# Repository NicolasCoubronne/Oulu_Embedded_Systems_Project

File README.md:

# Oulu_Embedded_Systems_Project

## Embedded System Project 2023, group 2

Clone :

git clone https://github.com/NicolasCoubronne/Oulu_Embedded_Systems_Project.git

Pull :

git pull

Push : 

git add *

git commit -m "name of commit"

<<<<<<< HEAD
git push origin main
=======
git push origin main
>>>>>>> 29aacac8a4f2100fd199b27751b34c95d99f8d8b

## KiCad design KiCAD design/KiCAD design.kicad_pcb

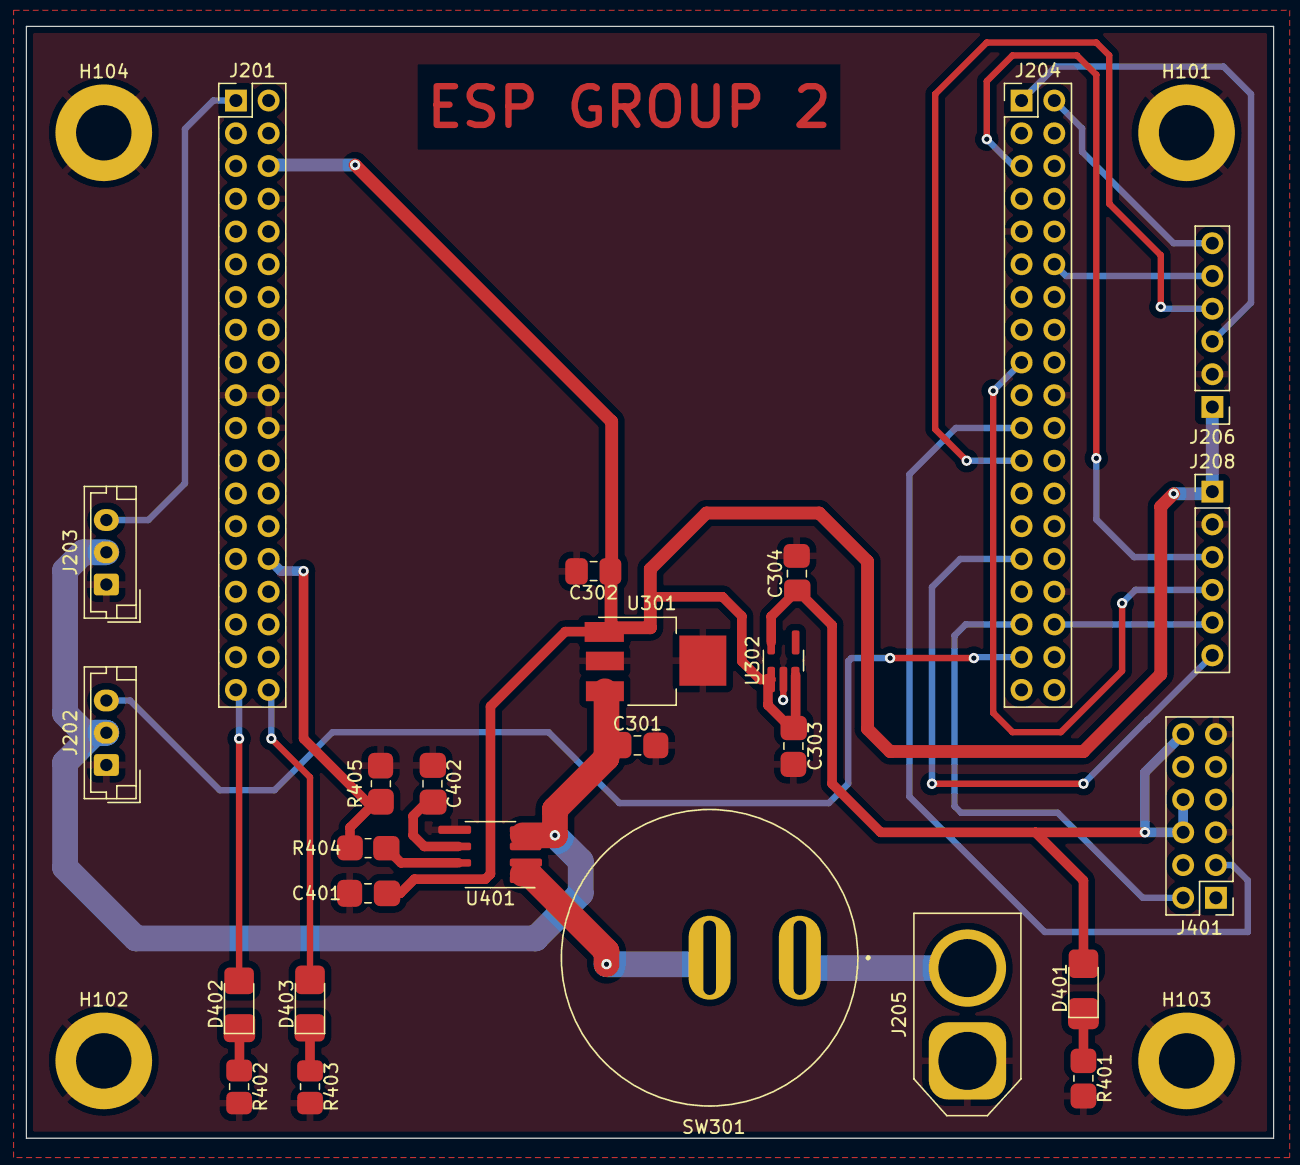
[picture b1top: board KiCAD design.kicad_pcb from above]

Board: 2 copper layers, 96.8 x 86.2 mm, 30 parts (0 on the bottom side), 26 nets.

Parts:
C301, C302, C303, C304: 1uF; C_0805_2012Metric
C401: 0.1uF; C_0805_2012Metric
C402: 1nF; C_0805_2012Metric
D401: GREEN; LED_1206_3216Metric
D402, D403: RED; LED_1206_3216Metric
H101, H102, H103, H104: MountingHole_Pad; MountingHole_4.3mm_M4_DIN965_Pad
J201, J204: Conn_02x19_Odd_Even; PinHeader_2x19_P2.54mm_Vertical
J202, J203: Conn_01x03_Female; JST_EH_B3B-EH-A_1x03_P2.50mm_Vertical
J205: JST BATTERY; AMASS_XT60-M_1x02_P7.20mm_Vertical
J206: JST SENS TOF 2; PinHeader_1x06_P2.54mm_Vertical
J208: JST SENS TOF 1; PinHeader_1x06_P2.54mm_Vertical
J401: Conn_02x06_Top_Bottom; PinHeader_2x06_P2.54mm_Vertical
R401, R402, R403: 330; R_0805_2012Metric
R404: 10k; R_0805_2012Metric
R405: 19.1k; R_0805_2012Metric
SW301: E-SWITCH_RR511D1121
U301: MCP1804T; SOT-223-3_TabPin2
U302: MIC5317; SOT-23-5
U401: ACS712xLCTR-20A; SOIC-8_3.9x4.9mm_P1.27mm

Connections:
+3.3V: C304.1, D401.2 (A), J401.6, J401.8, J401.12, U302.5 (VOUT)
+5V: C302.1, C303.1, C401.2, J201.6, J206.1, J208.1, U301.1 (OUT), U302.1 (VIN), U302.3 (~SHDN), U401.8 (VCC)
+12V: C301.1, J202.2, J203.2, U301.3 (IN), U401.3 (IP-), U401.4 (IP-)
/CONNECTORS/BATT: J205.2, SW301.1 (A)
/CONNECTORS/Bluetooth_RX: J204.33, J401.2
/CONNECTORS/Bluetooth_TX: J204.21, J401.3
/CONNECTORS/CURRENT_MEASURE: J201.30, R404.2, R405.1
/CONNECTORS/LED1: D403.2 (A), J201.38
/CONNECTORS/LED2: D402.2 (A), J201.37
/CONNECTORS/TOF1_DATA_READY: J204.29, J208.6
/CONNECTORS/TOF1_SCL: J204.17, J208.4
/CONNECTORS/TOF1_SDA: J204.5, J208.3
/CONNECTORS/TOF1_XSHUT: J204.34, J208.5
/CONNECTORS/TOF2_DATA_READY: J204.2, J206.6
/CONNECTORS/TOF2_SCL: J204.23, J206.4
/CONNECTORS/TOF2_SDA: J204.1, J206.3
/CONNECTORS/TOF2_XSHUT: J204.12, J206.5
/CONNECTORS/USART_HD_ARM: J202.3, J204.35
/CONNECTORS/USART_HD_BASE: J201.1, J203.3
/ON_BOARD_COMPONENTS/IP+: SW301.2 (B), U401.1 (IP+), U401.2 (IP+)
GND: C301.2, C302.2, C303.2, C304.2, C401.1, C402.1, H101.1, H102.1, H103.1, H104.1, J201.8, J201.19, J201.20, J201.22, J202.1, J203.1, J204.9, J204.20, J204.32, J205.1, J206.2, J208.2, J401.5, J401.11, R401.2, R402.2, R403.2, R405.2, U301.2 (GND), U302.2 (GND), U401.5 (GND)
unnamed: C402.2, U401.6 (FILTER)
unnamed: D401.1 (K), R401.1
unnamed: D402.1 (K), R402.1
unnamed: D403.1 (K), R403.1
unnamed: R404.1, U401.7 (VIOUT)

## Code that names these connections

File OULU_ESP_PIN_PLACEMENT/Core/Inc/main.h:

/* USER CODE BEGIN Header */
/**
  ******************************************************************************
  * @file           : main.h
  * @brief          : Header for main.c file.
  *                   This file contains the common defines of the application.
  ******************************************************************************
  * @attention
  *
  * Copyright (c) 2023 STMicroelectronics.
  * All rights reserved.
  *
  * This software is licensed under terms that can be found in the LICENSE file
  * in the root directory of this software component.
  * If no LICENSE file comes with this software, it is provided AS-IS.
  *
  ******************************************************************************
  */
/* USER CODE END Header */

/* Define to prevent recursive inclusion -------------------------------------*/
#ifndef __MAIN_H
#define __MAIN_H

#ifdef __cplusplus
extern "C" {
#endif

/* Includes ------------------------------------------------------------------*/
#include "stm32f4xx_hal.h"

/* Private includes ----------------------------------------------------------*/
/* USER CODE BEGIN Includes */

/* USER CODE END Includes */

/* Exported types ------------------------------------------------------------*/
/* USER CODE BEGIN ET */

/* USER CODE END ET */

/* Exported constants --------------------------------------------------------*/
/* USER CODE BEGIN EC */

/* USER CODE END EC */

/* Exported macro ------------------------------------------------------------*/
/* USER CODE BEGIN EM */

/* USER CODE END EM */

void HAL_TIM_MspPostInit(TIM_HandleTypeDef *htim);

/* Exported functions prototypes ---------------------------------------------*/
void Error_Handler(void);

/* USER CODE BEGIN EFP */

/* USER CODE END EFP */

/* Private defines -----------------------------------------------------------*/
#define B1_Pin GPIO_PIN_13
#define B1_GPIO_Port GPIOC
#define LED1_Pin GPIO_PIN_0
#define LED1_GPIO_Port GPIOC
#define LED2_Pin GPIO_PIN_3
#define LED2_GPIO_Port GPIOC
#define CURRENT_MEASURE_Pin GPIO_PIN_1
#define CURRENT_MEASURE_GPIO_Port GPIOA
#define USART_TX_ARM_Pin GPIO_PIN_2
#define USART_TX_ARM_GPIO_Port GPIOA
#define LD2_Pin GPIO_PIN_5
#define LD2_GPIO_Port GPIOA
#define TOF1_XHSUT_Pin GPIO_PIN_4
#define TOF1_XHSUT_GPIO_Port GPIOC
#define TOF2_DATA_READY_Pin GPIO_PIN_8
#define TOF2_DATA_READY_GPIO_Port GPIOC
#define TOF2_I2C_SDA_Pin GPIO_PIN_9
#define TOF2_I2C_SDA_GPIO_Port GPIOC
#define TOF2_I2C_SCL_Pin GPIO_PIN_8
#define TOF2_I2C_SCL_GPIO_Port GPIOA
#define BT_TX_Pin GPIO_PIN_9
#define BT_TX_GPIO_Port GPIOA
#define BT_RX_Pin GPIO_PIN_10
#define BT_RX_GPIO_Port GPIOA
#define TOF2_XSHUT_Pin GPIO_PIN_12
#define TOF2_XSHUT_GPIO_Port GPIOA
#define TMS_Pin GPIO_PIN_13
#define TMS_GPIO_Port GPIOA
#define TCK_Pin GPIO_PIN_14
#define TCK_GPIO_Port GPIOA
#define USART_TX_BASE_Pin GPIO_PIN_10
#define USART_TX_BASE_GPIO_Port GPIOC
#define SWO_Pin GPIO_PIN_3
#define SWO_GPIO_Port GPIOB
#define TOF1_DATA_READY_Pin GPIO_PIN_5
#define TOF1_DATA_READY_GPIO_Port GPIOB
#define TOF1_I2C_SCL_Pin GPIO_PIN_6
#define TOF1_I2C_SCL_GPIO_Port GPIOB
#define TOF1_I2C_SDA_Pin GPIO_PIN_9
#define TOF1_I2C_SDA_GPIO_Port GPIOB

/* USER CODE BEGIN Private defines */

/* USER CODE END Private defines */

#ifdef __cplusplus
}
#endif

#endif /* __MAIN_H */

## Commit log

2023-01-20 test
2023-03-07 readme
2023-03-07 Sheets and connectors
2023-03-14 finished conectors / sensors / converters
2023-03-14 labeling and add of components. STM32 pin selected
2023-03-15 servo extender piece (freecad + stl files)
2023-03-15 dont track backups and autosaves (they are different per system, will add changes even if you dont change anything and not needed in version control)
2023-03-15 forget ignored files
2023-03-17 correction pin bluetooth
2023-03-17 correction of errors
2023-03-17 add of footprint and nucleo as a reference
2023-03-17 track backups
2023-03-17 add BLUETOOTH_*X labels to bluetooth module
2023-03-17 voltage divider for current sensor
2023-03-19 add purchase location (field PurchaseLoc) and price (field Price) to some main components, adding rest later
2023-03-20 added PurchaseLoc and Price to most of the main components, leds, resistors, capacitors, switch, bluetooth missing
2023-03-20 Added LEDs
2023-03-21 dont track #auto_saved_files# cause it keeps getting added and deleted, that file is deleted when kicad closes
2023-03-21 add some comments, connector for battery, bluetooth (is now the PMOD BLE from digikey)
2023-03-21 add connector for Pmod BLE (HC05 connector still left)
2023-03-21 add comment for bluetooth connectors
2023-03-21 Added capacitors and resistors
2023-03-21 add link to switch and 1k resistor
2023-03-21 remove hc05 connector
2023-03-22 use . as decimal separator
2023-03-22 use individual prices
2023-03-22 better bom export script (check readme)
2023-03-22 Fixed info of 3 resistors in LED sheet
2023-03-23 current sensor VCC should be 5V
2023-03-23 10x larger resistors for voltage divider
2023-03-23 change led resistors to 330 ohm
2023-03-23 change voltage dividor resistors to larger dimensions
2023-03-24 Fixes
2023-03-25 more comments (no changes in functionality)
2023-03-25 restructure mechanical cad design dirs
2023-03-25 Year and group to readme
2023-03-28 comment about nucleo board in main sheet
2023-03-30 motor debug code dump
2023-04-03 change in nucleo pin
2023-04-04 kommentit
2023-04-04 fixed 3.3 voltage reg
2023-04-04 exclude mounting holes from BOM
2023-04-04 update BOM
2023-04-04 set same value for TOF sensor connectors to group them in BOM
2023-04-04 update lipo battery to something in stock
2023-04-04 change TOF sensor to one in stock (still VL53L0X, same pins)
2023-04-05 Added datasheets for TOF sensors
2023-04-05 end PCB
2023-04-06 debug code (will probably be wiped)
2023-04-06 Revert "merge?"
    This reverts commit 9507821d8c903603659f1e6f71c2fe75c77c06b3, reversing
    changes made to cc7a5d21546560b2c88e49b90c103b2912c9bd5f.
2023-04-06 fix reg 2.8->3.3
2023-04-06 remove mounting holse from bom
2023-04-06 tof sensor values and lipo bat
2023-04-06 tof sensor update
2023-04-06 debug changes
2023-04-06 begin writing functions for interfacint with ax12a
2023-04-06 ignore built files and stm32 settings
2023-04-07 continuation of nucleo-ax12a interface (untested)
2023-04-08 more ax functions
2023-04-08 expose more ax addresses for functions, should have most if not all that we need available now
2023-04-08 highlight that reset is actually factory reset
2023-04-08 comment most functions
2023-04-14 code shell
2023-04-14 KiCAD widening of copper pads
2023-04-14 fix byte order and initialization variable scope
2023-04-14 no need to calloc the buffers
2023-04-14 start with PMOD
2023-04-14 debug motoring misc.
2023-04-14 Demo software update
2023-04-14 add blocked move and stop functions
2023-04-14 no need to use uint16_t instead of unsigned int, let the compiler decide
2023-04-14 more uints16->unsigned int
2023-04-21 bluetooth code
2023-04-21 demo 2 + fix blocked move
2023-04-21 DMA Bluetooth
2023-04-21 DMA Bluetooth finish
2023-04-21 Modified PCB
2023-04-24 ignore freecad backups
2023-04-24 base support frame cad v1
2023-04-24 demo tof working
2023-04-25 fsm proto
2023-04-26 rename base support cad
2023-04-26 thicker & proper width base support
2023-04-26 demo updates
2023-04-26 Updated PCB and GRB files
2023-04-26 add states to sm
2023-04-26 track cprojects
2023-04-26 TOF implementation in motor
2023-04-26 integration bluetooth and TOF
2023-04-26 start angle
2023-04-26 finish initial angle find function
2023-04-26 increase support width + add holes
2023-04-26 add base and claw angles offset, caused by height offset
2023-04-26 make sure to use doubles
2023-05-05 test motor distance
2023-05-05 state machine OK
2023-05-12 add angle print debugging
2023-05-12 we dont need to abstract servo ids
2023-05-12 move defines to proper block
2023-05-12 asdf
2023-05-12 add servo angle diff function
2023-05-12 fsm and other improvements
2023-05-12 angle adjustments etc.
2023-05-12 led test
2023-05-17 stop servos at state change
2023-05-17 simplify blocked move
2023-05-17 further improve blocked move
2023-05-17 bluetooth abstraction and offset fixes
2023-05-17 comments
2023-05-17 more bt messages, template for operational led usage
2023-05-17 checks for bad object distance
2023-05-17 make uart send/recv return something if success/fail
2023-05-17 error led and current draw templates
2023-05-17 move onboard stuff to separate file
2023-05-17 pcb spacer
2023-05-17 fix width of spacer
2023-05-19 change tof sensor physical port
2023-05-19 tests
2023-05-19 final v1
2023-05-22 final v2
2023-05-23 remove double return
2023-05-23 mega commenet update
